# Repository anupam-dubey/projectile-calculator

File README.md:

# projectile-calculator
Projectile calculator based on nano and oled spi
## Project uses matrix keypad and oled display to show screen and user selection   
### program memory is used to save projectile data , stored data is converted from excel to array
#### and then imported by program

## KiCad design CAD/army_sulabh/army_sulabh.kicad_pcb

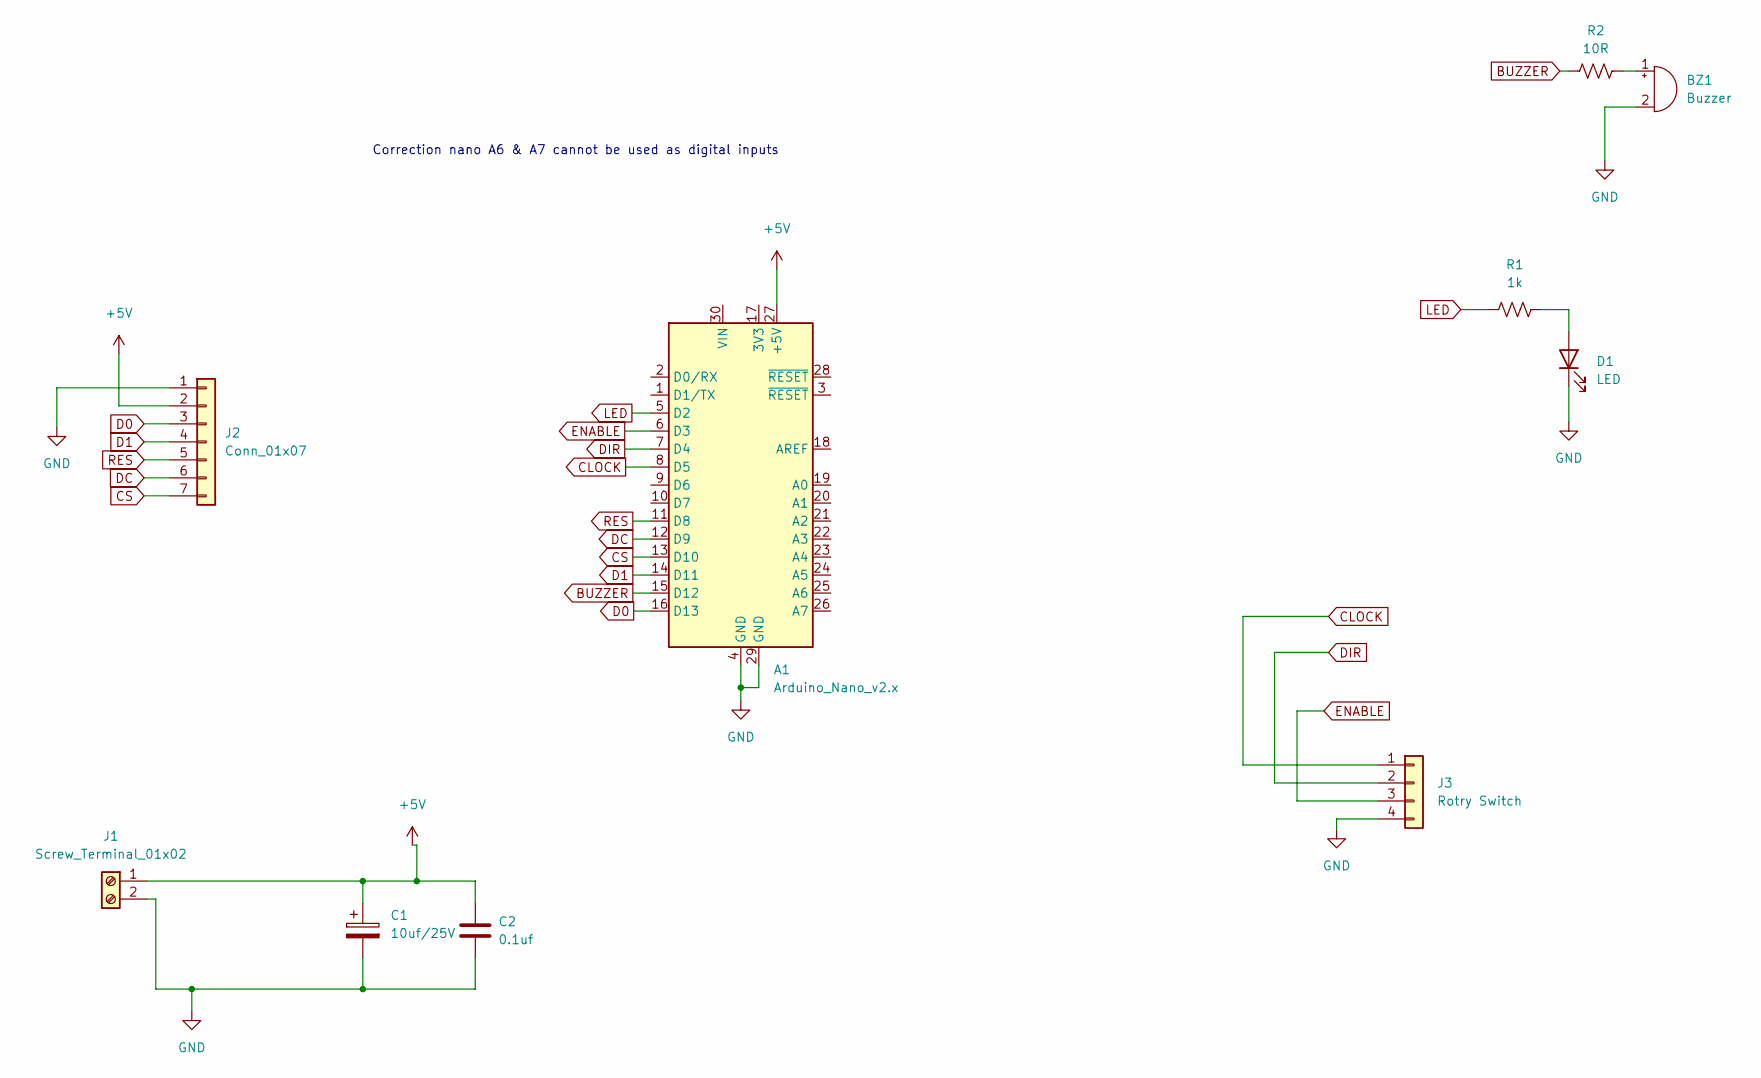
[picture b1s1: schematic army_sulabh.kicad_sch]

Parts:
A1: Arduino_Nano_v2.x; Arduino_Nano
BZ1: Buzzer; Buzzer_12x9.5RM7.6
C1: 10uf/25V; CP_Radial_D5.0mm_P2.50mm
C2: 0.1uf; C_Disc_D5.0mm_W2.5mm_P5.00mm
D1: LED; LED_D3.0mm_FlatTop
J1: Screw_Terminal_01x02; TerminalBlock_Phoenix_MKDS-1,5-2_1x02_P5.00mm_Horizontal
J2: Conn_01x07; PinHeader_1x07_P2.54mm_Vertical
J3: Rotry Switch; PinHeader_1x04_P2.54mm_Vertical
R1: 1k; R_Axial_DIN0207_L6.3mm_D2.5mm_P10.16mm_Horizontal
R2: 10R; R_Axial_DIN0207_L6.3mm_D2.5mm_P10.16mm_Horizontal

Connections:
+5V: A1.27 (+5V), C1.1, C2.1, J1.1, J2.2
BUZZER: A1.15 (D12), R2.2
CLOCK: A1.8 (D5), J3.1
CS: A1.13 (D10), J2.7
D0: A1.16 (D13), J2.3
D1: A1.14 (D11), J2.4
DC: A1.12 (D9), J2.6
DIR: A1.7 (D4), J3.2
ENABLE: A1.6 (D3), J3.3
GND: A1.4 (GND), A1.29 (GND), BZ1.2 (+), C1.2, C2.2, D1.1 (K), J1.2, J2.1, J3.4
LED: A1.5 (D2), R1.2
unnamed: BZ1.1 (-), R2.1
unnamed: D1.2 (A), R1.1
RES: A1.11 (D8), J2.5

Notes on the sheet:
Correction nano A6 & A7 cannot be used as digital inputs

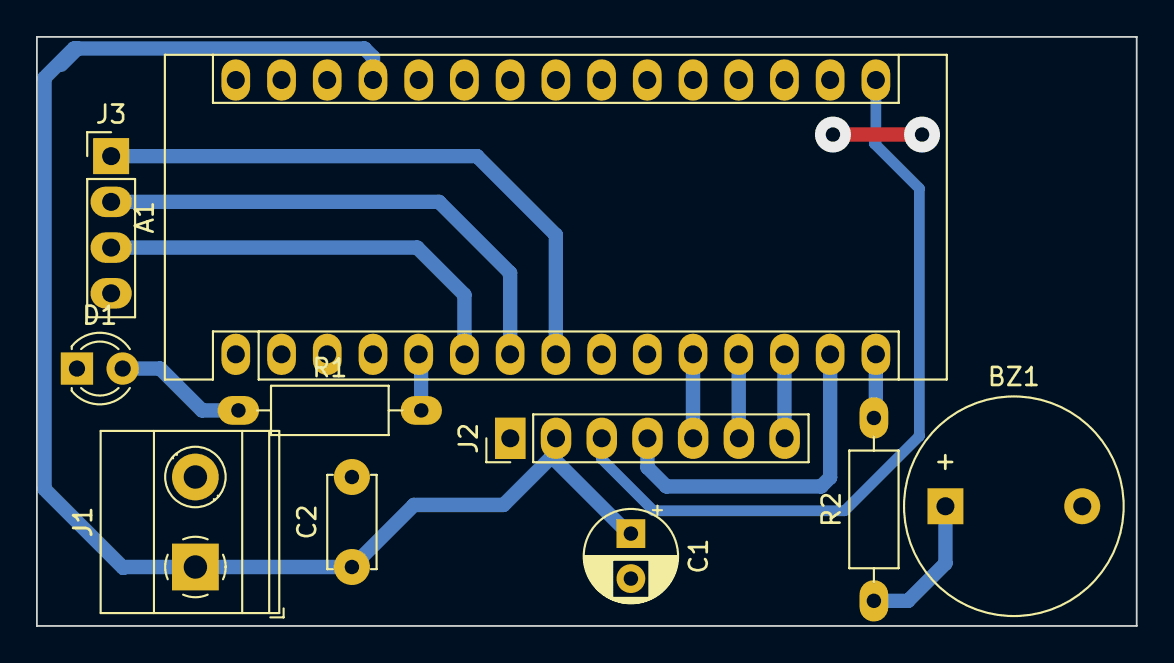
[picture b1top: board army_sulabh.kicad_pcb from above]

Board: 2 copper layers, 61.1 x 32.7 mm, 10 parts (0 on the bottom side), 14 nets.

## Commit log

2023-02-14 first
